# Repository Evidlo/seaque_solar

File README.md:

# seaque_solar

Design files for [SEAQUE](https://research.physics.illinois.edu/QI/Photonics/SEAQUE/) solar experiment.

# Files

- `board/` - KiCAD design files for IV sweeper
- `firmware/` - STM32 software for downlinking through SEAQUE
- `analysis/` - post-downlink analysis software

# Pics

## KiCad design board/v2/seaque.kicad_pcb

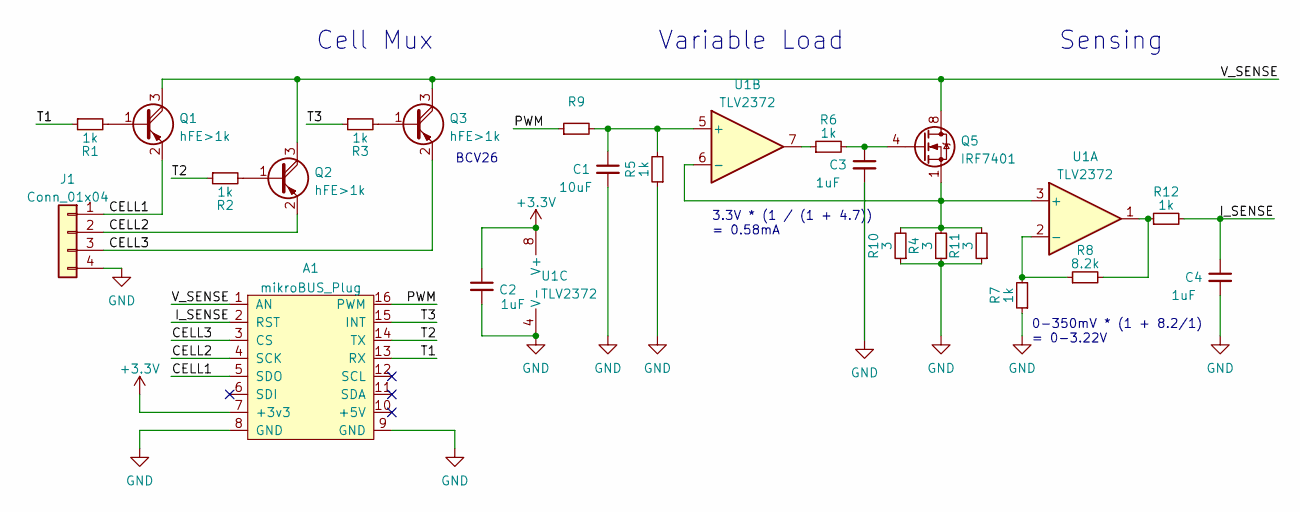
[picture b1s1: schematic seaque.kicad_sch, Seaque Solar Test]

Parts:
A1: mikroBUS_Plug
C1: 10uF; C_0603_1608Metric_Pad1.08x0.95mm_HandSolder
C2, C3, C4: 1uF; C_0603_1608Metric_Pad1.08x0.95mm_HandSolder
J1: Conn_01x04; Molex_Pico-Lock_504050-0491_1x04-1MP_P1.50mm_Horizontal
Q1, Q2, Q3: hFE>1k; SOT-23_Handsoldering
Q5: IRF7401; SOIC-8_3.9x4.9mm_P1.27mm
R1, R2, R3, R5, R6, R7, R12: 1k; C_0603_1608Metric_Pad1.08x0.95mm_HandSolder
R4, R10, R11: 3; C_0603_1608Metric_Pad1.08x0.95mm_HandSolder
R8: 8.2k; C_0603_1608Metric_Pad1.08x0.95mm_HandSolder
R9: C_0603_1608Metric_Pad1.08x0.95mm_HandSolder
U1: TLV2372; SOIC-8_3.9x4.9mm_P1.27mm

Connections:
+3V3: A1.7 (+3v3), C2.1, U1.8 (V+)
/CELL1: A1.5 (SDO), J1.1, Q1.2 (E)
/CELL2: A1.4 (SCK), J1.2, Q2.2 (E)
/CELL3: A1.3 (CS), J1.3, Q3.2 (E)
/I_SENSE: A1.2 (RST), C4.1, R12.2
/PWM: A1.16 (PWM), R9.1
/T1: A1.13 (RX), R1.1
/T2: A1.14 (TX), R2.1
/T3: A1.15 (INT), R3.1
/V_SENSE: A1.1 (AN), Q1.3 (C), Q2.3 (C), Q3.3 (C), Q5.5 (D), Q5.6 (D), Q5.7 (D), Q5.8 (D)
GND: A1.8 (GND), A1.9 (GND), C1.2, C2.2, C3.2, C4.2, J1.4, R4.1, R5.1, R7.1, R10.1, R11.1, U1.4 (V-)
unnamed: C1.1, R5.2, R9.2, U1.5 (+)
unnamed: C3.1, Q5.4 (G), R6.2
unnamed: Q1.1 (B), R1.2
unnamed: Q2.1 (B), R2.2
unnamed: Q3.1 (B), R3.2
unnamed: R6.1, U1.7
unnamed: R7.2, R8.1, U1.2 (-)
unnamed: R8.2, R12.1, U1.1
unnamed: Q5.1 (S), Q5.2 (S), Q5.3 (S), R4.2, R10.2, R11.2, U1.3 (+), U1.6 (-)

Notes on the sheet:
0-350mV * (1 + 8.2/1) = 0-3.22V
Cell Mux
Variable Load
BCV26
Sensing
3.3V * (1 / (1 + 4.7)) = 0.58mA

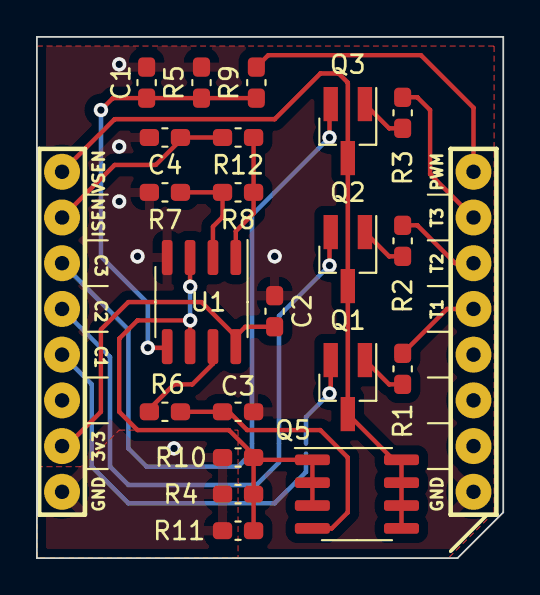
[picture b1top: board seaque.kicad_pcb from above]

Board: 2 copper layers, 25.9 x 29.0 mm, 23 parts (1 on the bottom side), 20 nets.

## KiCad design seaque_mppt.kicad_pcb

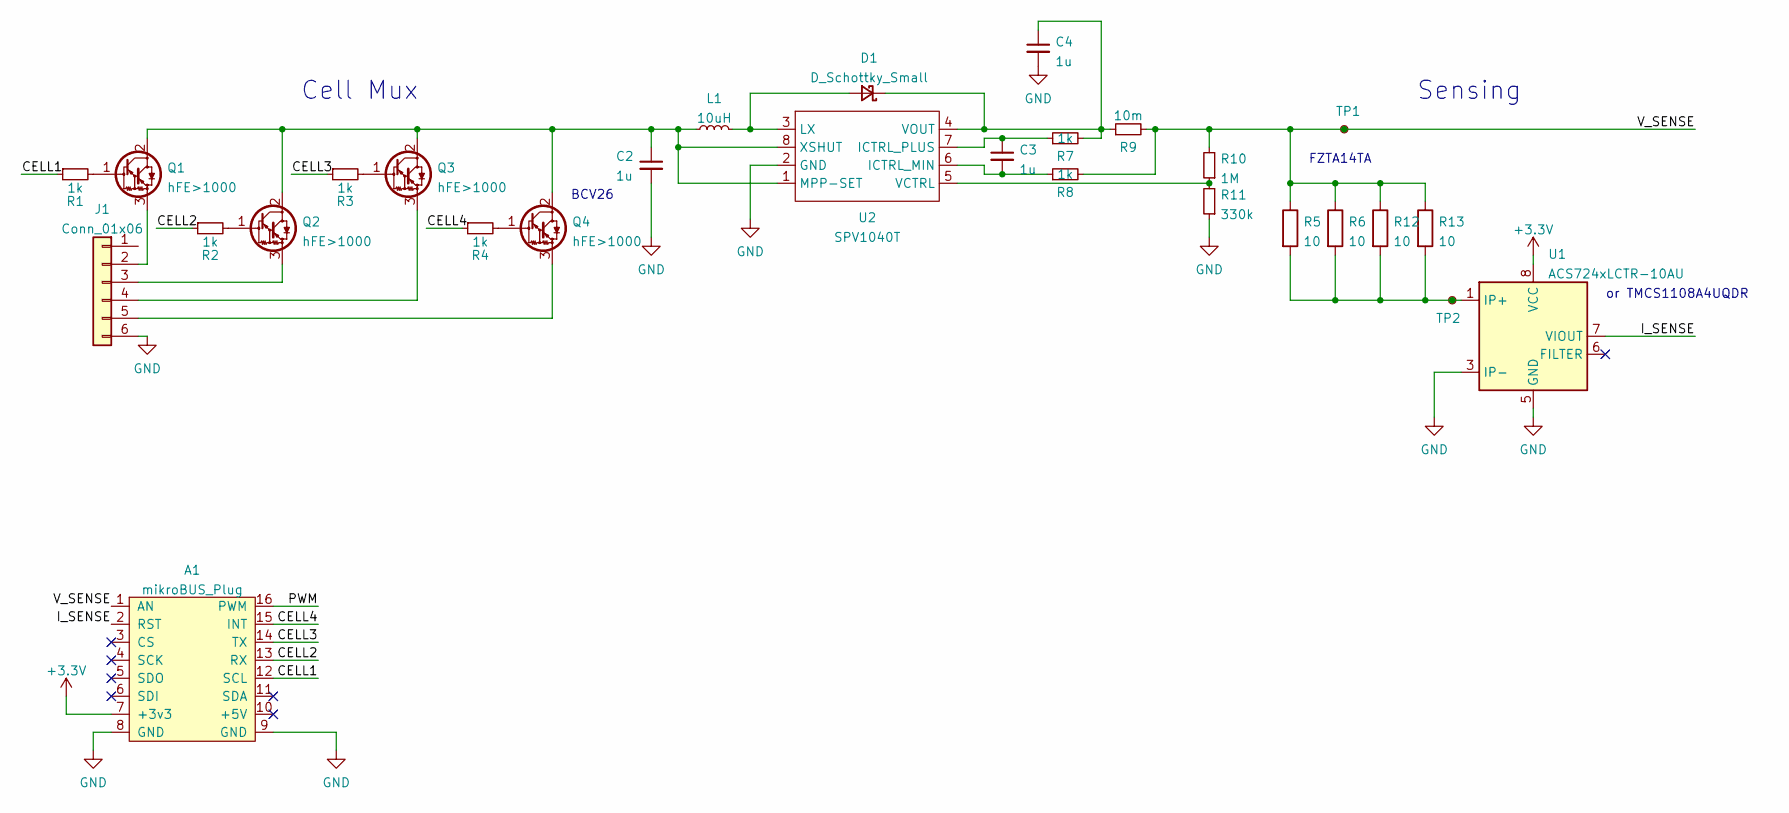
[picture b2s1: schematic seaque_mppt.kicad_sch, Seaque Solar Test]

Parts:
A1: mikroBUS_Plug
C2, C3, C4: 1u; C_0603_1608Metric
D1: D_Schottky_Small; D_SMA
J1: Conn_01x06; Molex_Pico-Lock_504050-0591_1x05-1MP_P1.50mm_Horizontal
L1: 10uH; L_6.3x6.3_H3
Q1, Q2, Q3, Q4: hFE>1000; SC-59_Handsoldering
R1, R2, R3, R4, R7, R8: 1k; R_0603_1608Metric
R5, R6, R12, R13: 10; R_1206_3216Metric
R9: 10m; R_0603_1608Metric
R10: 1M; R_0603_1608Metric
R11: 330k; R_0603_1608Metric
TP1, TP2: TestPoint_Small; PinHeader_1x01_P1.00mm_Vertical
U1: ACS724xLCTR-10AU; SOIC-8_3.9x4.9mm_P1.27mm
U2: SPV1040T; TSSOP-8_4.4x3mm_P0.65mm

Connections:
+3V3: A1.7 (+3v3), U1.8 (VCC)
/CELL1: A1.12 (SCL), R1.1
/CELL2: A1.13 (RX), R2.1
/CELL3: A1.14 (TX), R3.1
/CELL4: A1.15 (INT), R4.1
/I_SENSE: A1.2 (RST), U1.7 (VIOUT)
/PWM: A1.16 (PWM)
/V_SENSE: A1.1 (AN), R5.1, R6.1, R8.2, R9.2, R10.2, R12.1, R13.1, TP1.1
GND: A1.8 (GND), A1.9 (GND), C2.2, C4.2, J1.1, J1.6, R11.1, U1.3 (IP-), U1.4 (IP-), U1.5 (GND), U2.2 (GND)
unnamed: C2.1, L1.1, Q1.2 (C), Q2.2 (C), Q3.2 (C), Q4.2 (C), U2.1 (MPP-SET), U2.8 (XSHUT)
unnamed: C3.1, R7.1, U2.7 (ICTRL_PLUS)
unnamed: C3.2, R8.1, U2.6 (ICTRL_MIN)
unnamed: C4.1, D1.1 (K), R7.2, R9.1, U2.4 (VOUT)
unnamed: D1.2 (A), L1.2, U2.3 (LX)
unnamed: J1.2, Q1.3 (E)
unnamed: J1.3, Q2.3 (E)
unnamed: J1.4, Q3.3 (E)
unnamed: J1.5, Q4.3 (E)
unnamed: Q1.1 (B), R1.2
unnamed: Q2.1 (B), R2.2
unnamed: Q3.1 (B), R3.2
unnamed: Q4.1 (B), R4.2
unnamed: R10.1, R11.2, U2.5 (VCTRL)
unnamed: R5.2, R6.2, R12.2, R13.2, TP2.1, U1.1 (IP+), U1.2 (IP+)

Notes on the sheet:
Cell Mux
or TMCS1108A4UQDR
BCV26
FZTA14TA
Sensing

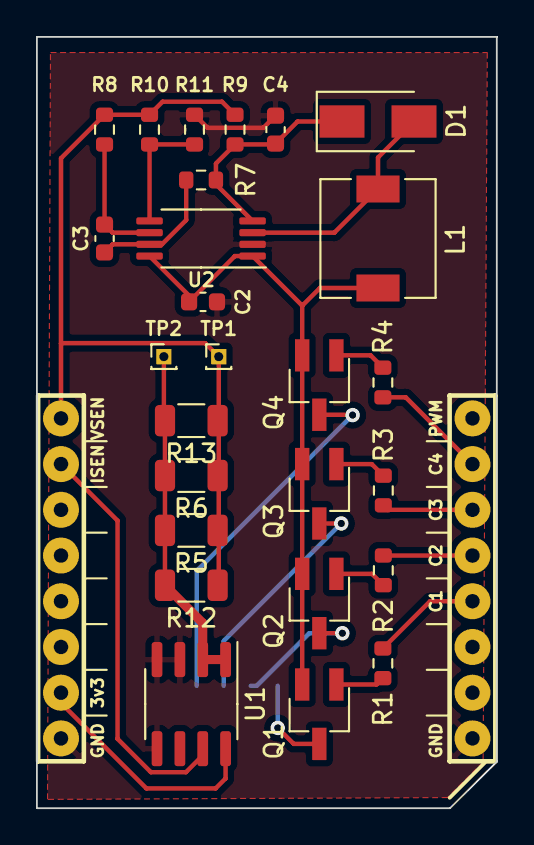
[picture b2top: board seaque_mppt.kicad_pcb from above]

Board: 2 copper layers, 25.5 x 42.9 mm, 28 parts (1 on the bottom side), 23 nets.

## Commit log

2022-02-22 updated MPPT board
2023-02-05 init commit
2026-02-23 final commit
2026-02-23 update images
2026-02-23 reorganize data
